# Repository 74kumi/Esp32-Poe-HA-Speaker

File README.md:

# ESP32 PoE Home Assistant Speaker

A PoE-powered network ceiling-speaker controller built around an **ESP32-S3**, **W5500 Ethernet**, **PCM5122 DAC**, and **TPA3116D2 amplifier**.

The long-term goal is a retrofit-friendly Home Assistant / voice-assistant speaker platform: reuse ordinary ceiling speakers, add network audio and control at the speaker, and optionally add a modular microphone-array ring hidden behind the existing grille.

## Project disclaimer

I'm not a hardware engineer — I'm an IT administrator who enjoys electronics, Home Assistant, and building things. I have a working understanding of many of the concepts involved, but this project has also been developed heavily with AI-assisted design, CAD scripting, and review.

I would genuinely welcome review or collaboration from experienced hardware engineers, especially as the project moves toward its first physical prototype.

The finalized engineering handoff is now archived in this repository, but the hardware has not yet been fabricated, assembled, or electrically validated. I cannot claim that the current design will work as intended. Please treat it as an engineering prototype and manufacturing handoff, not a proven product.

> **RevF manufacturing release:** this is the finalized manufacturing handoff for the RevE PCB design. The electrical CAD revision remains RevE for traceability; RevF identifies the released manufacturing package.
>
> The supplied package was reviewed and verified by an engineer according to the project owner. That review evidence is preserved with the handoff, but it does not replace independent source-file review, fabrication, assembly, or prototype validation. PCBWay should confirm the final 4-layer stack-up and 100 Ω Ethernet impedance before production.

## Project status

| Area | Status |
| --- | --- |
| Main-board schematic / PCB | Rev E finalized engineered source archived |
| Main-board manufacturing release | RevF handoff archived with Gerbers, drills, BOM, CPL, STEP, and notes |
| KiCad source | Rev E source available directly in this repository |
| Main-board saved ERC / DRC | Supplied release reports included; profile-dependent and not a substitute for independent validation |
| Ethernet layout | Finalized: 0.2764 mm / 0.20 mm target geometry; fabricator stack-up confirmation remains |
| Power / protection | Finalized engineering handoff; bench startup, fault, current, and thermal validation remain |
| Audio / amplifier | Circuit, thermal, and acoustic validation still required |
| Firmware | ESP32 Voice Home Assistant firmware target; bring-up not yet complete |
| Home Assistant integration | ESP32 Voice Home Assistant integration planned after hardware bring-up |
| Microphone array | Six-microphone RGB ring engineered handoff archived; prototype and acoustic validation remain |
| Physical prototype | Not built yet; fabrication package prepared |

A clean ERC/DRC result is a regression check, not proof that the circuit is electrically correct, safe, acoustically suitable, or production-ready.

## Current hardware

The main board is intended to provide:

- ESP32-S3 controller
- wired Ethernet using W5500
- PoE-powered operation with bench-power support for development
- PCM5122 playback DAC
- TPA3116D2 speaker amplifier
- target of approximately **30 W into 4 ohms**, subject to real prototype validation
- programming / debug access
- expansion interfaces, including the reserved J4 microphone-ring connector

### Current Rev E board preview

The image above reflects the current Rev E board source more closely than the historical 3D render at the top of this README. The KiCad files remain the authoritative design reference.

### Open the Rev E design

The active source is tracked directly in Git:

- [Rev E KiCad project](hardware/PoE-Speaker/RevE/KiCad-RevE/PoE-Speaker-RevE.kicad_pro)
- [Rev E PCB](hardware/PoE-Speaker/RevE/KiCad-RevE/PoE-Speaker-RevE.kicad_pcb)
- [Rev E schematic](hardware/PoE-Speaker/RevE/KiCad-RevE/PoE-Speaker-RevE.kicad_sch)
- [Rev E engineering notes](hardware/PoE-Speaker/RevE/engineering/)
- [RevF manufacturing package](hardware/PoE-Speaker/RevF/Manufacturing/README-PCBWay.md)
- [RevF board preview](board-revf.png)
- [Historical design checkpoints](hardware/checkpoints/)

Open the project in **KiCad 10**. Keep the adjacent project-local footprint library, symbol library, tables, design rules, BOM, and generated netlist together.

## Modular microphone rings

The project now includes a supplied, engineer-reviewed six-microphone RGB ring handoff. It is separate from the main PoE board and is intended to connect through the main-board J4 expansion interface. The ring package includes KiCad source, custom libraries, BOM, placement data, Gerbers, drills, STEP models, datasheets, design notes, and engineering reports.

- [Microphone-ring concept and status](hardware/microphone-rings/README.md)
- [Final six-microphone RGB ring handoff](hardware/microphone-rings/ESP32-S3-Microphone-RGB-Ring/)
- [Listening / status-light plan](hardware/microphone-rings/LED-STATUS-LIGHT-PLAN.md)
- [Main-board J4 connector definition](hardware/PoE-Speaker/RevE/engineering/CONNECTOR-GUIDE.md)

The archived ring is a six-microphone engineered design; it should not be described as an already validated eight-microphone production system. Electrical bring-up, cable/interface validation, mechanical fit, microphone performance, vibration behavior, and acoustic/echo testing remain outstanding.

## Engineering status and roadmap

The current release state is **final engineered PCB handoffs archived**:

- Main board: RevE editable CAD with a RevF manufacturing release package.
- Microphone ring: six-microphone RGB engineered handoff with manufacturing outputs.
- Provenance: supplied final files, reports, and supporting evidence are preserved; embedded history repositories, lock files, and editor session artifacts were excluded.

Remaining work before production approval includes:

1. Confirm the PCBWay 4-layer stack-up, finished thickness, copper assumptions, and 100 Ω Ethernet impedance.
2. Fabricate and assemble a prototype from the RevF handoff.
3. Execute controlled PoE, bench-power, startup, protection, Ethernet, regulator, DAC, amplifier, thermal, and fault testing.
4. Bring up the six-microphone ring through J4 and validate its power, clock/data, I2C/RGB control, cable behavior, and connector pinout.
5. Measure microphone response, vibration coupling, grille fit, acoustic shadowing, simultaneous playback behavior, and echo-cancellation requirements.
6. Complete the ESP32 Voice Home Assistant firmware bring-up and Home Assistant integration after the hardware interfaces are validated.

Project documents:

- [Roadmap](ROADMAP.md)
- [Engineering review guide](ENGINEERING-REVIEW.md)
- [Order / release review](ORDER-RELEASE-REVIEW.md)
- [Prototype validation plan](PROTOTYPE-VALIDATION.md)
- [Contribution guidance](CONTRIBUTING.md)
- [GitHub issues](https://github.com/74kumi/Esp32-Poe-HA-Speaker/issues)

## Repository layout

```text
.
├── docs/
│   ├── HISTORY.md
│   └── images/
│       └── early-board-render.png
├── hardware/
│   ├── PoE-Speaker/
│   │   ├── RevE/
│   │   │   ├── KiCad-RevE/        # current editable board source
│   │   │   └── engineering/       # design reviews, calculations and scripts
│   │   └── RevF/Manufacturing/    # fabrication and assembly release outputs
│   ├── microphone-rings/
│   │   ├── ESP32-S3-Microphone-RGB-Ring/ # engineered ring handoff
│   │   └── README.md              # concept, interface, and validation status
│   └── checkpoints/               # historical board revisions
├── ENGINEERING-REVIEW.md
├── ORDER-RELEASE-REVIEW.md
├── PROTOTYPE-VALIDATION.md
├── ROADMAP.md
└── board-top.png
```

## Contributing / reviewing

Engineering review is welcome, especially around Ethernet signal integrity, protection / fault behavior, power conversion, amplifier implementation, thermal design, footprints, acoustic performance, and manufacturability.

When reporting a hardware finding, please include the affected revision, component / pin / net, location where practical, expected behavior, observed concern, and supporting datasheet section or calculation. Clearly distinguish confirmed defects from questions or suggested improvements.

See [CONTRIBUTING.md](CONTRIBUTING.md) for the current review priorities and main-board change policy.

This project has used AI-assisted CAD scripting and review workflows. AI output is not treated as engineering validation; independent review and physical prototype measurements are still required.

## License

Original hardware design materials are available for personal, educational, research, and other noncommercial use under the terms in [LICENSE](LICENSE).

Commercial manufacture, sale, OEM use, paid integration, or other commercial exploitation requires a separate written commercial license from the copyright holder.

Software, firmware, scripts, and third-party material may be subject to separate terms. Vendor references, library content, trademarks, and datasheets retain their respective owners' rights and notices.

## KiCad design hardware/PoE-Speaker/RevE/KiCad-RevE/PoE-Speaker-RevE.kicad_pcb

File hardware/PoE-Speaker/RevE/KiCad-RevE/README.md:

# Revision E — prototype review checkpoint

Open PoE-Speaker-RevE.kicad_pro in KiCad 10. This is the latest editable board. Earlier revisions remain preserved. NOT APPROVED FOR ORDERING OR POWER-UP.

Saved changes: C11 GVDD bypass is now local on B.Cu at (204.9,111.5), preserving the R15 PLIMIT branch; underside assembly clearance remains part of mechanical review. U7 FSW now connects to 3V3 per TI guidance; all previously missing passive/header order codes have documented candidates; C120/C121 use stable 100nF 100V C0G 1210 parts and C122 uses a 1uF 100V 1210 part. C17/C18 are a matched 2.2uF 25V pair. U5 is TPA3116D2DADR, U9/U10 are LM5050MK-2/NOPB, and Ag5800 is confirmed as the complete U1 code. Corrected 34 footprint assembly attributes and widened 51 power segments to 0.8mm where existing clearance permits.

Validation: zero DRC findings, zero unconnected items, zero ERC findings under the saved rule profile. All 616 connected model pins match schematic and PCB. U6/U7 electrical pin types are reviewed; the root sheet declares power sources after passive elements. These annotations do not prove circuit performance, and other imported pin types remain incomplete. See reports/power-source-review.json. Missing courtyard and some metadata checks remain disabled in the inherited profile; clean DRC does not substitute for physical review.

## Automated ERC/DRC checks

From the repository root, run:

```sh
KICAD_CLI=kicad-cli ./scripts/run-kicad-checks.sh artifacts/kicad
```

The wrapper writes `erc.rpt` and `drc.rpt`. GitHub Actions runs the same command for pull requests and pushes to `main`, retaining reports for 14 days. CI uses KiCad 10.0.5 from the immutable image `kicad/kicad:10.0.5@sha256:182c8005cb775a2c448a4c18681d489f1ff472a761885eba3e08b07e3c0564de`; use KiCad 10.0.5 for local runs when exact CI parity is required. The checks require zero KiCad ERC/DRC violations and do not run DRC after an ERC failure. Project-specific engineering/checkpoint scripts are intentionally excluded from CI because many are board-mutating, depend on checkpoint-local tools/data, or have not yet been proven read-only and reproducible in a clean CI environment.

Clean checks do not prove electrical correctness, PoE isolation, Ethernet signal integrity, thermal safety, manufacturability, or fabrication readiness.

Remaining work before a prototype order:

1. Reroute the remaining narrow loaded power paths, review via current capacity and local switching loops. reports/power-routing-audit.json contains exact positions and UUIDs; separate low-current sense branches from load trunks before modifying them. The two longest 24V_AMP sections (49.385mm and 39.837mm) have now been rerouted at 1.0mm width. A new continuous 1.0mm feed from C5 to the amplifier supply bypasses the congested narrow branch using two 0.5mm drilled vias. The original branch remains in parallel. See engineering/REVE-TRUNK-ROUTING.md; the whole path is not yet current-qualified.
2. Qualify Ethernet differential routing against the explicit JLC04161H-7628 design baseline and verify continuous return paths. See engineering/ETHERNET-STACKUP.md; the calculator-derived Ethernet100 routing preset is saved, but copper still needs rerouting and fabrication confirmation.
3. Review input fuse/transient coordination, capacitor effective capacitance and regulator stability, and amplifier supply tolerance. F1 DC interrupt ratings are now sourced; source/fault and time-current coordination remain open (engineering/FUSE-RATING-REVIEW.md).
4. Fit a top heatsink to the TPA3116D2 DAD package, check the Ag5800 thermal interface, body clearances, mounting support and connector access. H3/H4 now support the extended right edge at x=275; use insulating M2 standoffs. Thirteen assembly components still need verified courtyard/body review.
5. Produce and inspect Gerber, drill, assembly BOM and placement files only after those design checks; obtain fabricator stackup/via-treatment constraints. No manufacturing files or order submission are included in this checkpoint.

After assembly: staged current-limited bring-up, rail/startup/overload measurements, firmware and audio/Ethernet tests. Those are prototype validation activities, not prerequisites that can be completed without hardware. The eight-microphone ring remains a future separate board; this board is not a completed eight-microphone capture system.

Preserve routing: do not run build_revision.py or build_efuse_revision.py over this folder. For schematic-only updates run refresh_prototype_schematic.py, then annotate_prototype_power.py, export netlist/ERC and run validate_prototype.py. Editing model metadata alone does not update the schematic.

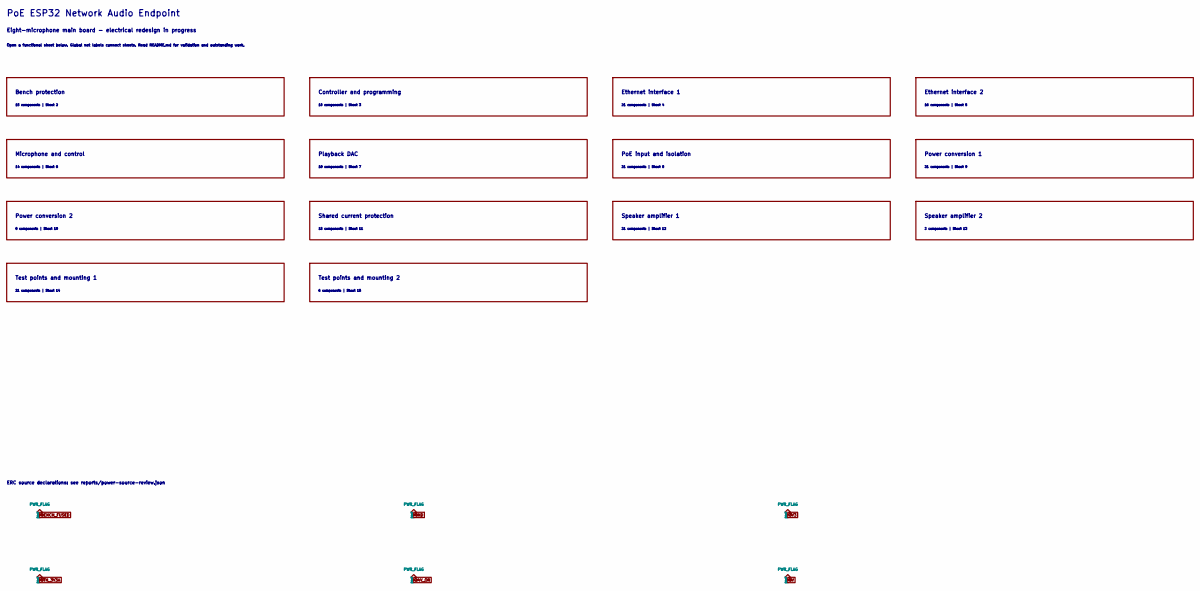
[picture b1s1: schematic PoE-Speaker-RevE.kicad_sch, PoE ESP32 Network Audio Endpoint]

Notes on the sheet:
ERC source declarations: see reports/power-source-review.json
21 components | Sheet 8
Microphone and control
Test points and mounting 1
15 components | Sheet 11
21 components | Sheet 14
21 components | Sheet 12
2 components | Sheet 13
14 components | Sheet 6
Bench protection
18 components | Sheet 7
21 components | Sheet 9
16 components | Sheet 5
Power conversion 1
15 components | Sheet 2
Speaker amplifier 1
Open a functional sheet below. Global net labels connect sheets. Read README.md for validation and outstanding work.
Ethernet interface 2
PoE ESP32 Network Audio Endpoint
Speaker amplifier 2
Shared current protection
Eight-microphone main board - electrical redesign in progress
PoE input and isolation
Playback DAC
Ethernet interface 1
6 components | Sheet 15
Power conversion 2
21 components | Sheet 4
Test points and mounting 2
Controller and programming
8 components | Sheet 10
10 components | Sheet 3

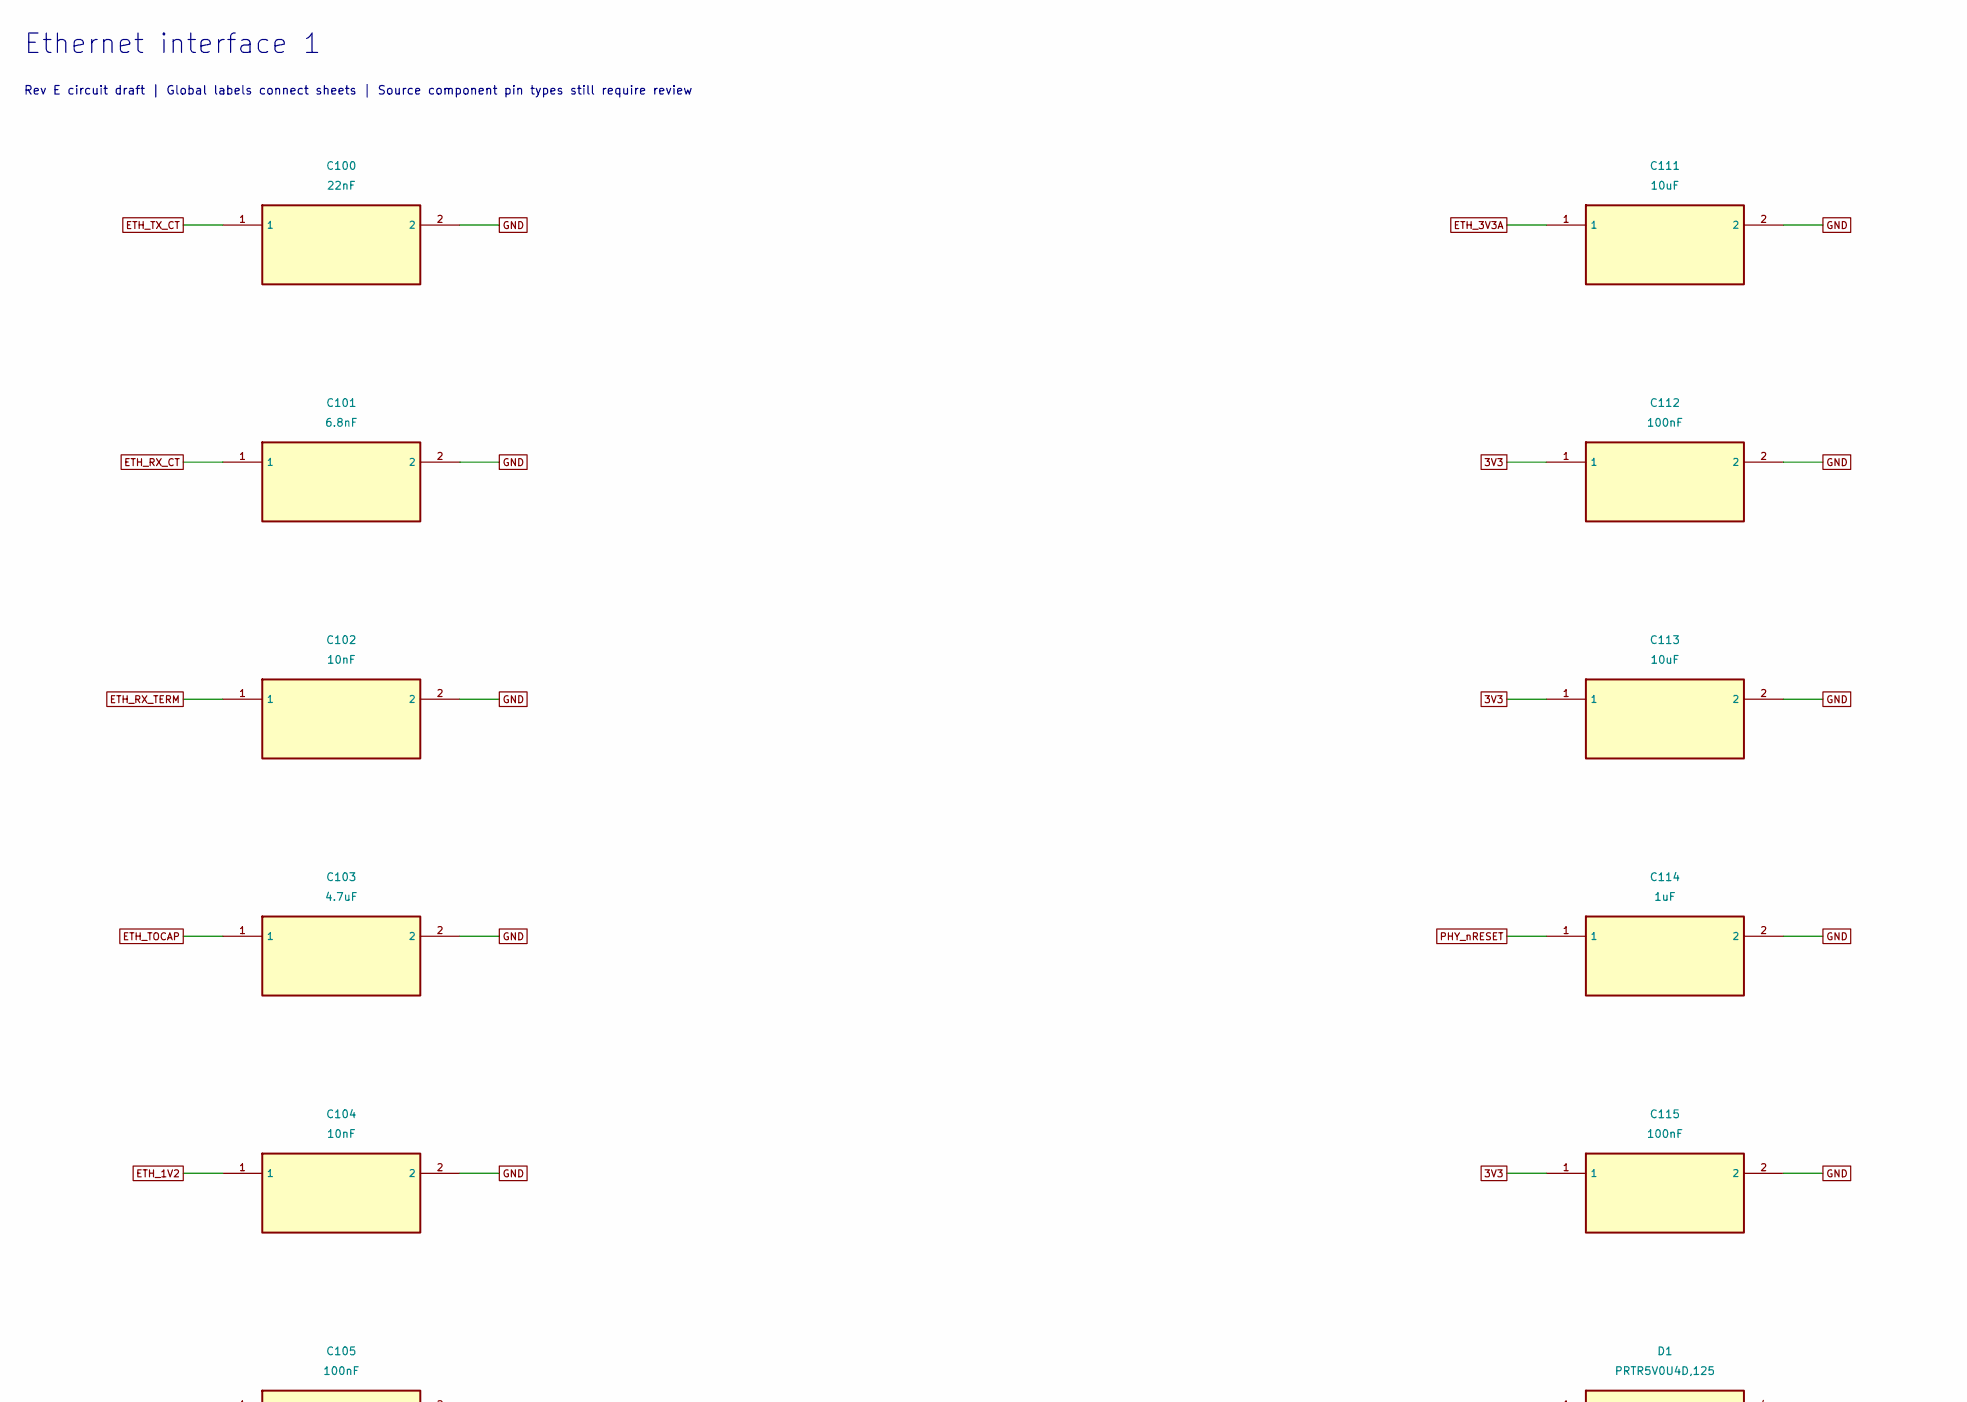
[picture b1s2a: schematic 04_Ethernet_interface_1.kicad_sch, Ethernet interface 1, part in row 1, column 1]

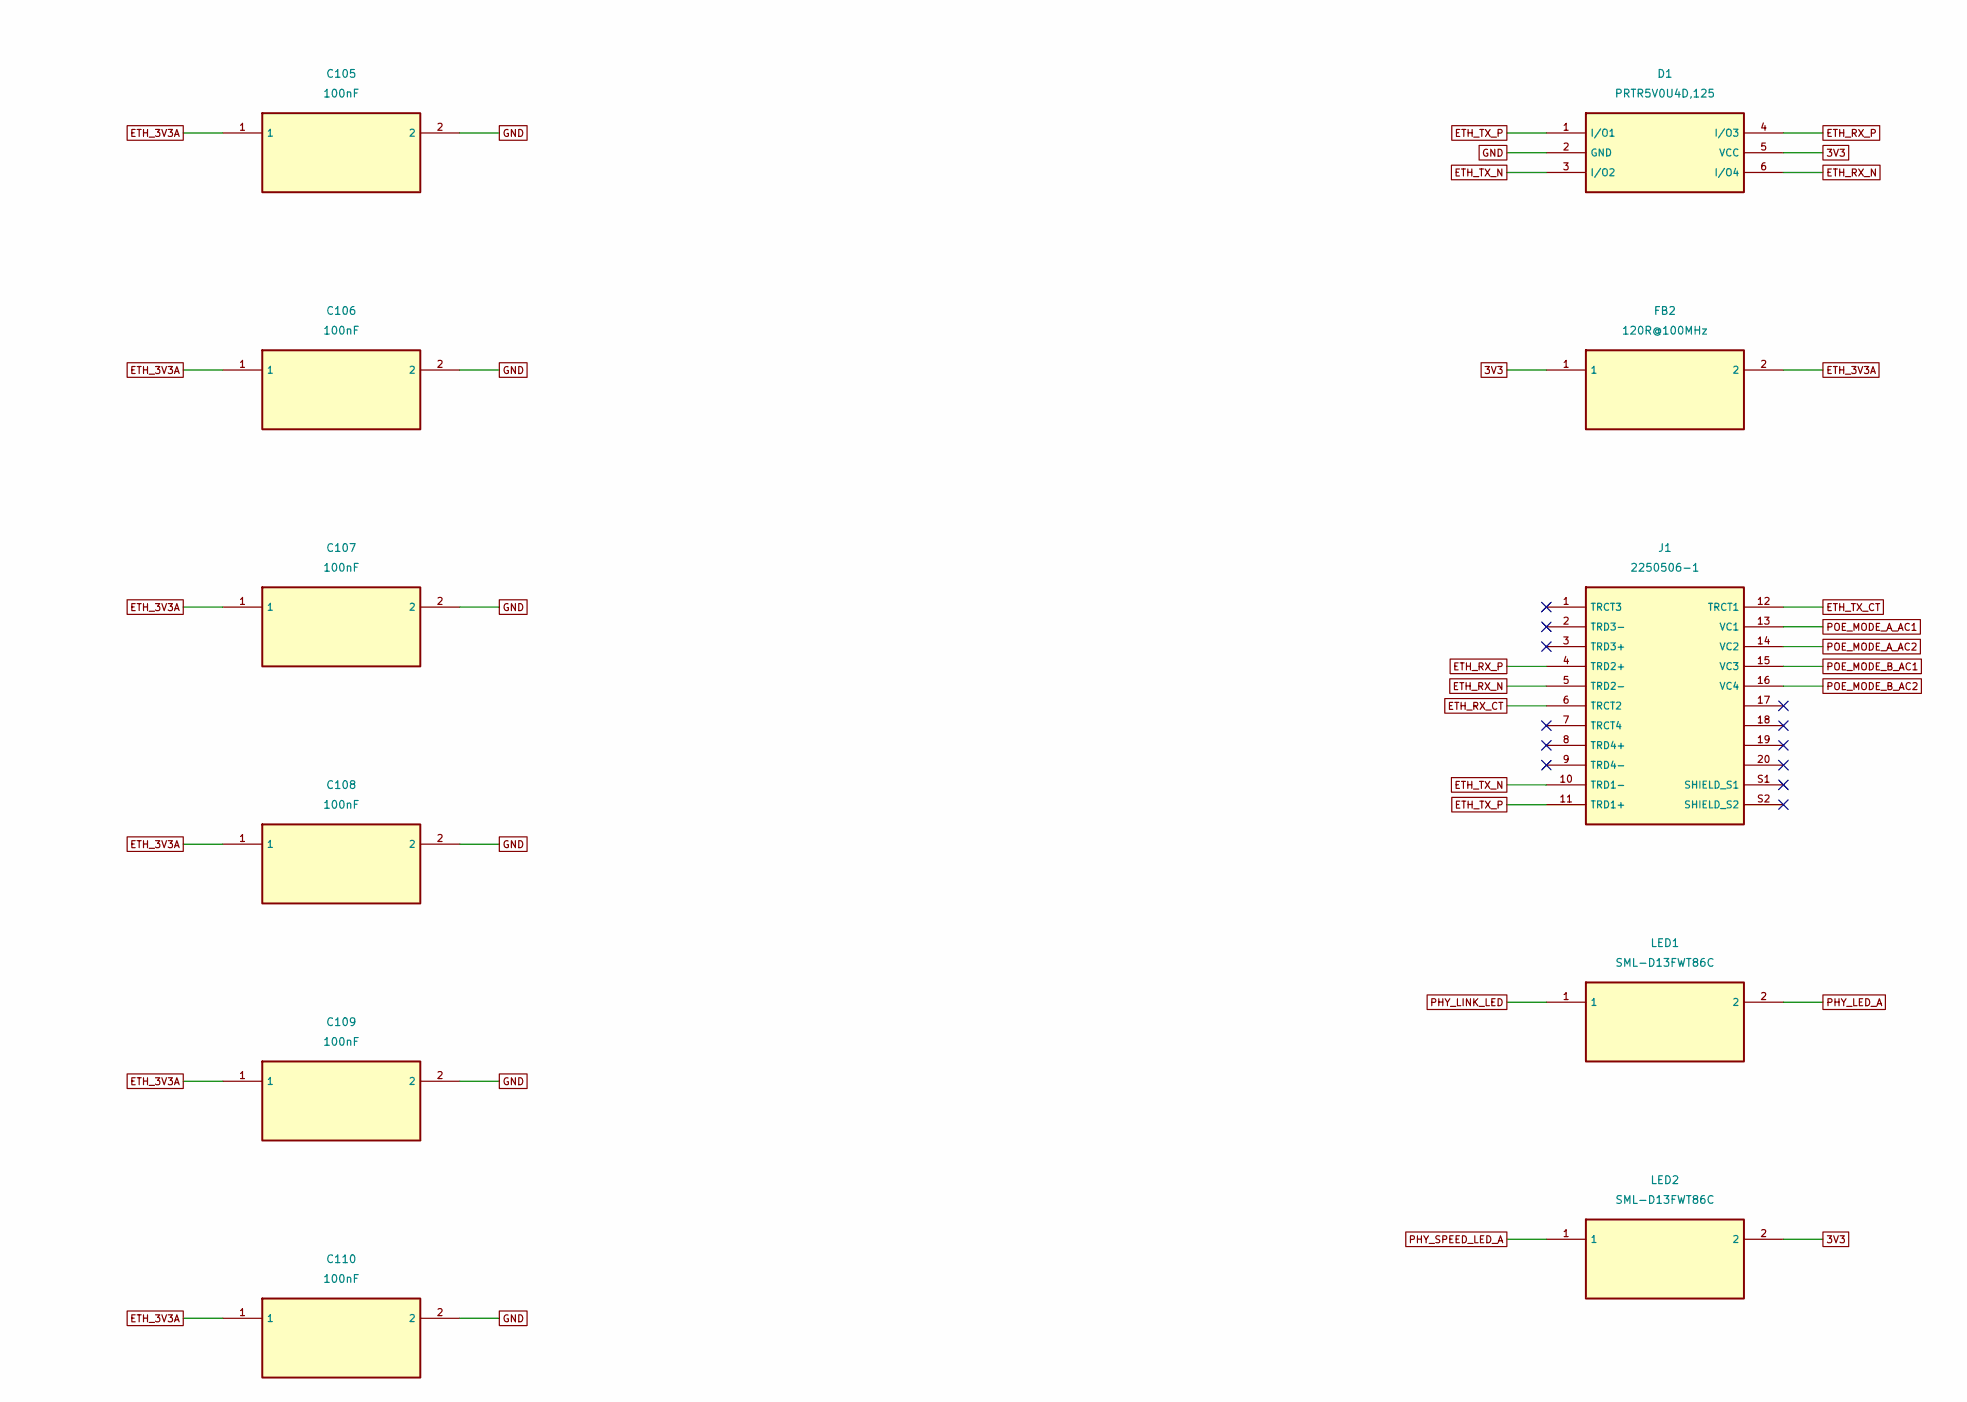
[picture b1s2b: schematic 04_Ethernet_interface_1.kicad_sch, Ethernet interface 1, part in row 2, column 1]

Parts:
C100: 22nF; C100_RevB; Voltage Rating 50 V; Tolerance 10%; Manufacturer Part Number C0603C223K5RACTU
C101: 6.8nF; C101_RevB; Voltage Rating 50 V; Tolerance 5%; Manufacturer Part Number C0603C682J5GACTU
C102: 10nF; C102_RevB; Voltage Rating 50 V; Tolerance 10%; Manufacturer Part Number C0603C103K5RACTU
C103: 4.7uF; C103_RevB; Voltage Rating 16 V; Tolerance 10%; Manufacturer Part Number C0805C475K4RACTU
C104: 10nF; C104_RevB; Voltage Rating 50 V; Tolerance 10%; Manufacturer Part Number C0603C103K5RACTU
C105: 100nF; C105_RevB; Voltage Rating 50 V; Tolerance 10%; Manufacturer Part Number C0603C104K5RACTU
C106: 100nF; C106_RevB; Voltage Rating 50 V; Tolerance 10%; Manufacturer Part Number C0603C104K5RACTU
C107: 100nF; C107_RevB; Voltage Rating 50 V; Tolerance 10%; Manufacturer Part Number C0603C104K5RACTU
C108: 100nF; C108_RevB; Voltage Rating 50 V; Tolerance 10%; Manufacturer Part Number C0603C104K5RACTU
C109: 100nF; C109_RevB; Voltage Rating 50 V; Tolerance 10%; Manufacturer Part Number C0603C104K5RACTU
C110: 100nF; C110_RevB; Voltage Rating 50 V; Tolerance 10%; Manufacturer Part Number C0603C104K5RACTU
C111: 10uF; C111_RevB; Voltage Rating 16 V; Tolerance 10%; Manufacturer Part Number GRM21BR61C106KE15L
C112: 100nF; C112_RevB; Voltage Rating 50 V; Tolerance 10%; Manufacturer Part Number C0603C104K5RACTU
C113: 10uF; C113_RevB; Voltage Rating 16 V; Tolerance 10%; Manufacturer Part Number GRM21BR61C106KE15L
C114: 1uF; C114_RevB; Voltage Rating 16 V; Tolerance 10%; Manufacturer Part Number C0603C105K4RACTU
C115: 100nF; C115_RevB; Voltage Rating 50 V; Tolerance 10%; Manufacturer Part Number C0603C104K5RACTU
D1: PRTR5V0U4D,125; D1_RevB; Manufacturer Part Number PRTR5V0U4D,125
FB2: 120R@100MHz; FB2_RevB; Manufacturer Part Number BLM18PG121SN1D
J1: 2250506-1; J1_RevB; Manufacturer Part Number 2250506-1
LED1: SML-D13FWT86C; LED1_RevB; Manufacturer Part Number SML-D13FWT86C
LED2: SML-D13FWT86C; LED2_RevB; Manufacturer Part Number SML-D13FWT86C

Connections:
3V3: C112.1, C113.1, C115.1, D1.5 (VCC), FB2.1, LED2.2; also elsewhere on the board
ETH_1V2: C104.1; also elsewhere on the board
ETH_3V3A: C105.1, C106.1, C107.1, C108.1, C109.1, C110.1, C111.1, FB2.2; also elsewhere on the board
ETH_RX_CT: C101.1, J1.6 (TRCT2)
ETH_RX_N: D1.6 (I/O4), J1.5 (TRD2-); also elsewhere on the board
ETH_RX_P: D1.4 (I/O3), J1.4 (TRD2+); also elsewhere on the board
ETH_RX_TERM: C102.1; also elsewhere on the board
ETH_TOCAP: C103.1; also elsewhere on the board
ETH_TX_CT: C100.1, J1.12 (TRCT1); also elsewhere on the board
ETH_TX_N: D1.3 (I/O2), J1.10 (TRD1-); also elsewhere on the board
ETH_TX_P: D1.1 (I/O1), J1.11 (TRD1+); also elsewhere on the board
GND: C100.2, C101.2, C102.2, C103.2, C104.2, C105.2, C106.2, C107.2, C108.2, C109.2, C110.2, C111.2, C112.2, C113.2, C114.2, C115.2, D1.2 (GND); also elsewhere on the board
PHY_LED_A: LED1.2; also elsewhere on the board
PHY_LINK_LED: LED1.1; also elsewhere on the board
PHY_SPEED_LED_A: LED2.1; also elsewhere on the board
PHY_nRESET: C114.1; also elsewhere on the board
POE_MODE_A_AC1: J1.13 (VC1); also elsewhere on the board
POE_MODE_A_AC2: J1.14 (VC2); also elsewhere on the board
POE_MODE_B_AC1: J1.15 (VC3); also elsewhere on the board
POE_MODE_B_AC2: J1.16 (VC4); also elsewhere on the board

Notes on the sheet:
Ethernet interface 1
Rev E circuit draft | Global labels connect sheets | Source component pin types still require review

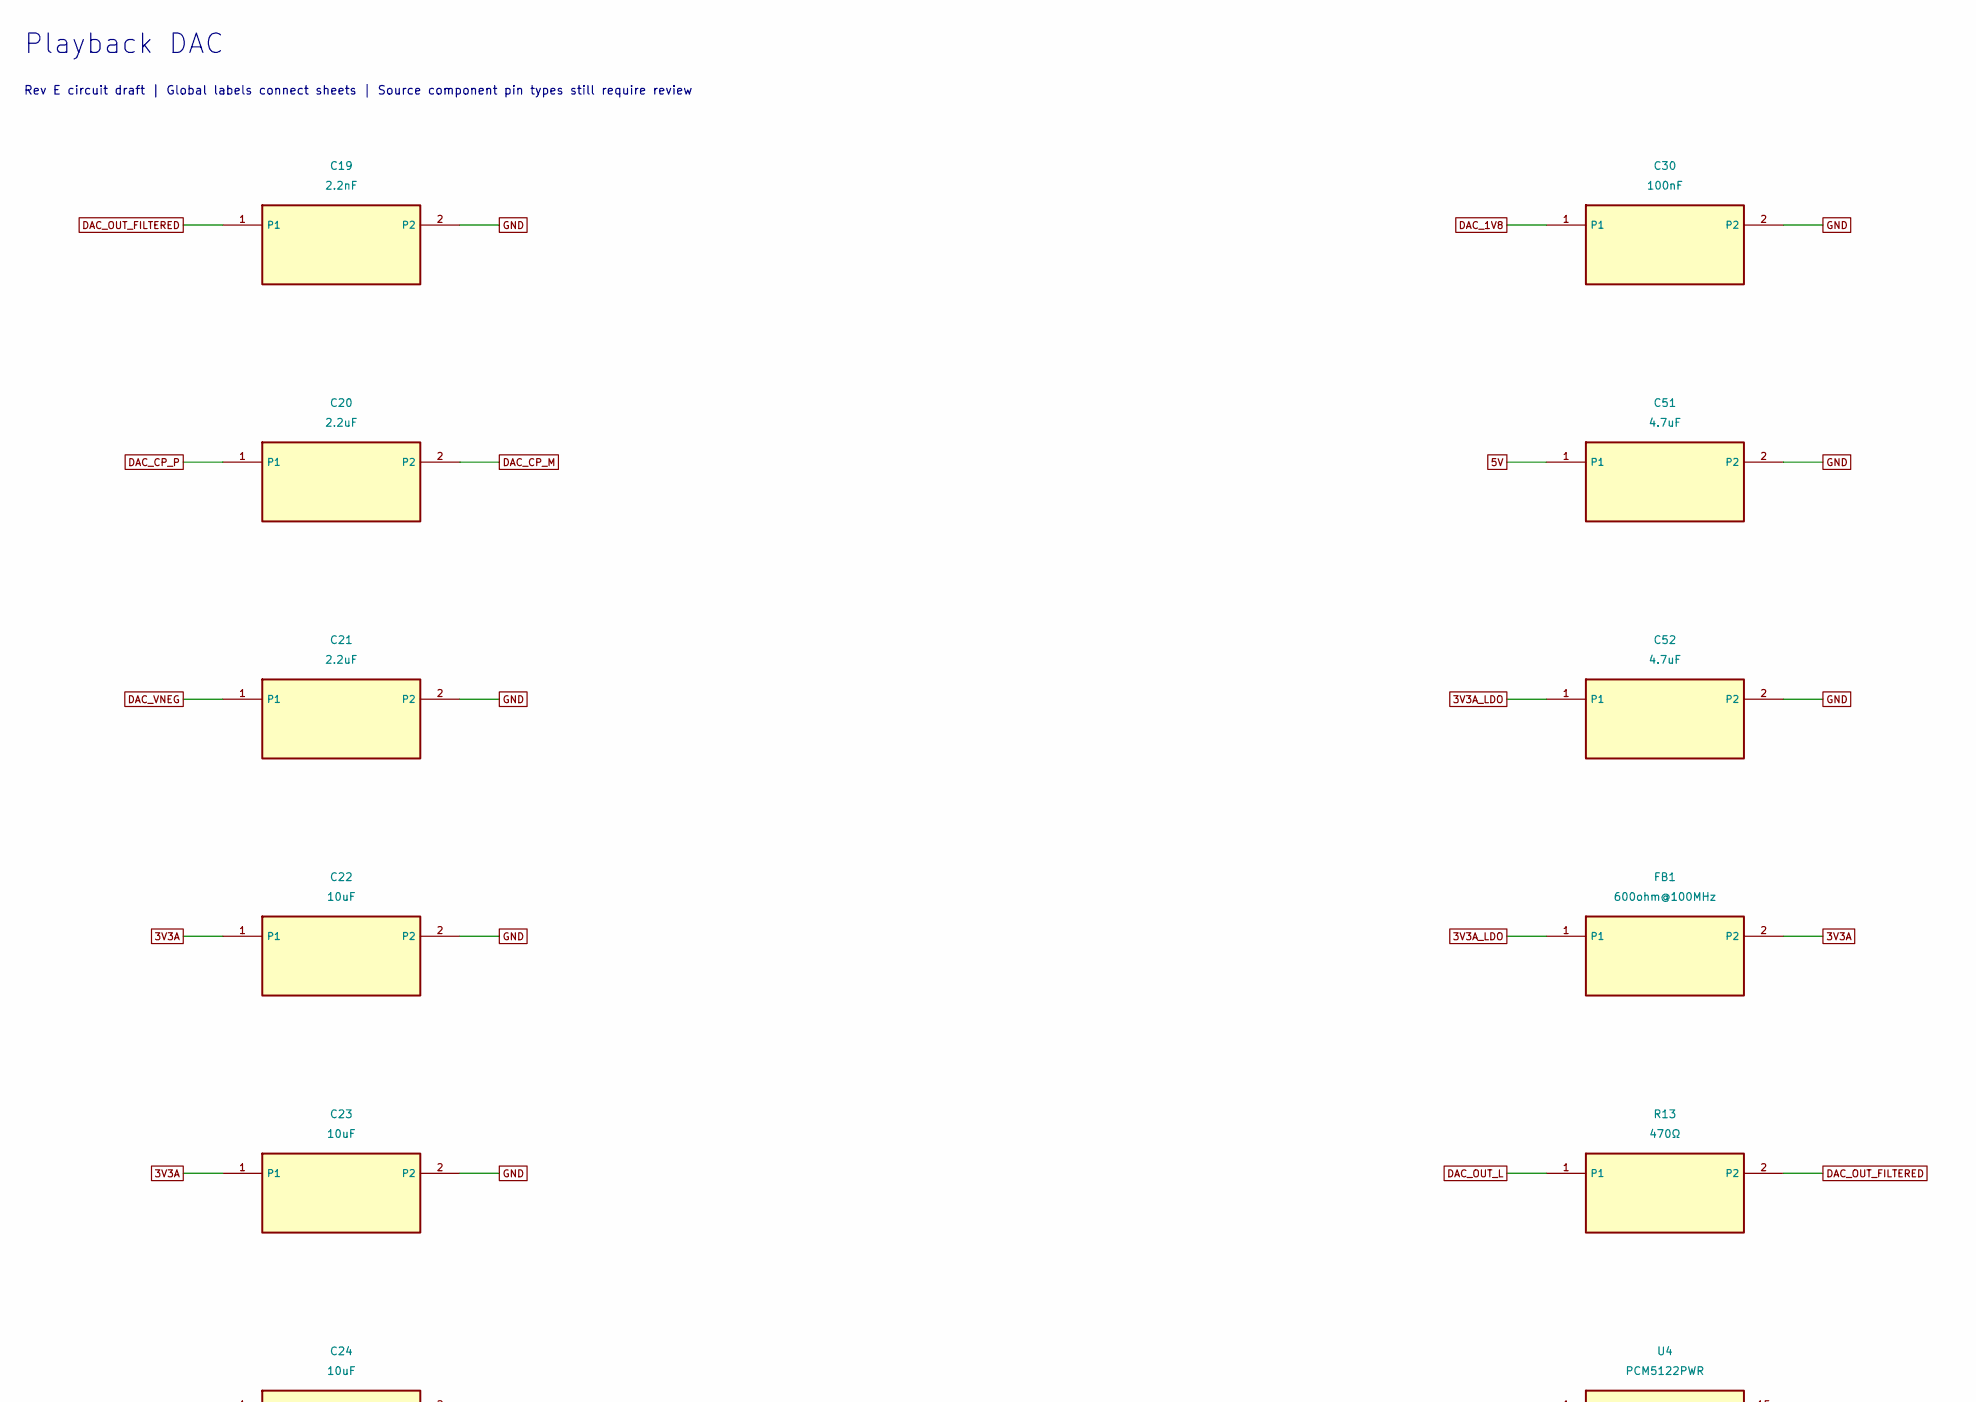
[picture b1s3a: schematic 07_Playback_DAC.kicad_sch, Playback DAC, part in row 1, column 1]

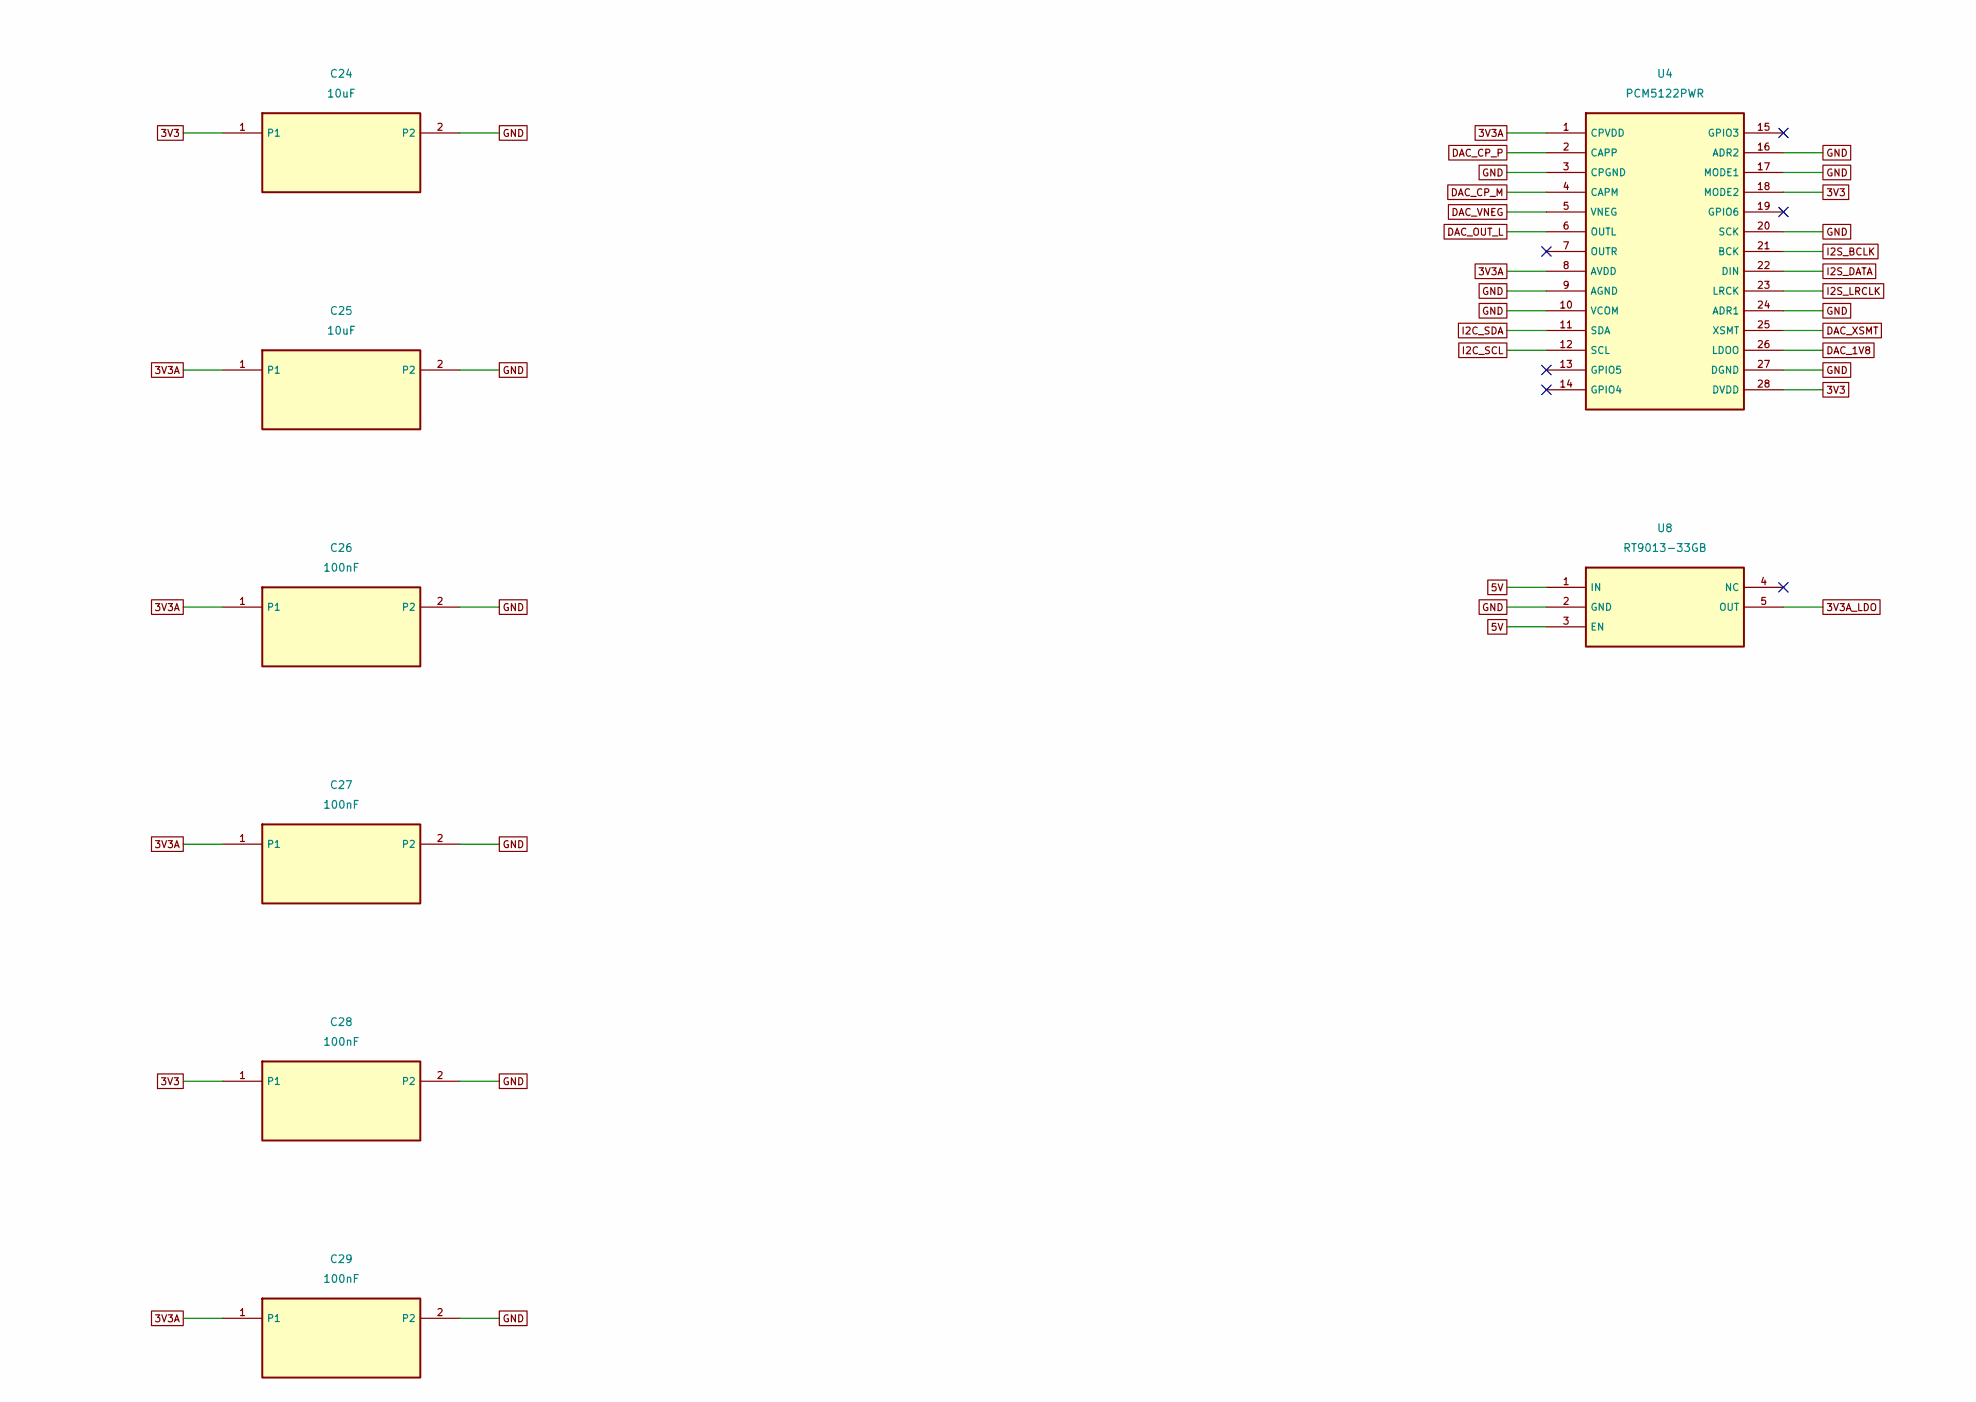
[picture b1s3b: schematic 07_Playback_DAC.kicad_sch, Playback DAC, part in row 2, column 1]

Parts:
C19: 2.2nF; C19_RevB; Voltage Rating 50 V; Tolerance 5%; Manufacturer Part Number C0603C222J5GACTU
C20: 2.2uF; C20_RevB; Voltage Rating 25 V; Tolerance 10%; Manufacturer Part Number C0805C225K3RACTU
C21: 2.2uF; C21_RevB; Voltage Rating 25 V; Tolerance 10%; Manufacturer Part Number C0805C225K3RACTU
C22: 10uF; C22_RevB; Voltage Rating 16 V; Tolerance 10%; Manufacturer Part Number GRM21BR61C106KE15L
C23: 10uF; C23_RevB; Voltage Rating 16 V; Tolerance 10%; Manufacturer Part Number GRM21BR61C106KE15L
C24: 10uF; C24_RevB; Voltage Rating 16 V; Tolerance 10%; Manufacturer Part Number GRM21BR61C106KE15L
C25: 10uF; C25_RevB; Voltage Rating 16 V; Tolerance 10%; Manufacturer Part Number GRM21BR61C106KE15L
C26: 100nF; C26_RevB; Voltage Rating 50 V; Tolerance 10%; Manufacturer Part Number C0603C104K5RACTU
C27: 100nF; C27_RevB; Voltage Rating 50 V; Tolerance 10%; Manufacturer Part Number C0603C104K5RACTU
C28: 100nF; C28_RevB; Voltage Rating 50 V; Tolerance 10%; Manufacturer Part Number C0603C104K5RACTU
C29: 100nF; C29_RevB; Voltage Rating 50 V; Tolerance 10%; Manufacturer Part Number C0603C104K5RACTU
C30: 100nF; C30_RevB; Voltage Rating 50 V; Tolerance 10%; Manufacturer Part Number C0603C104K5RACTU
C51: 4.7uF; C51_RevB; Voltage Rating 16 V; Tolerance 10%; Manufacturer Part Number C0805C475K4RACTU
C52: 4.7uF; C52_RevB; Voltage Rating 16 V; Tolerance 10%; Manufacturer Part Number C0805C475K4RACTU
FB1: 600ohm@100MHz; FB1_RevB; Current Rating 0.5A; Current rating 500 mA; Part Type Inductor
R13: 470Ω; R13_RevB; Tolerance 1%; Power rating 0.10 W conservative; Part Type Resistor
U4: PCM5122PWR; U4_RevB; Part Type Digital To Analog Converters (DACs); JLCPCB Part Class Extended Part
U8: RT9013-33GB; U8_RevB; Manufacturer Part Number RT9013-33GB

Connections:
3V3: C24.1, C28.1, U4.18 (MODE2), U4.28 (DVDD); also elsewhere on the board
3V3A: C22.1, C23.1, C25.1, C26.1, C27.1, C29.1, FB1.2, U4.1 (CPVDD), U4.8 (AVDD); also elsewhere on the board
3V3A_LDO: C52.1, FB1.1, U8.5 (OUT)
5V: C51.1, U8.1 (IN), U8.3 (EN); also elsewhere on the board
DAC_1V8: C30.1, U4.26 (LDOO)
DAC_CP_M: C20.2, U4.4 (CAPM)
DAC_CP_P: C20.1, U4.2 (CAPP)
DAC_OUT_FILTERED: C19.1, R13.2; also elsewhere on the board
DAC_OUT_L: R13.1, U4.6 (OUTL)
DAC_VNEG: C21.1, U4.5 (VNEG)
DAC_XSMT: U4.25 (XSMT); also elsewhere on the board
GND: C19.2, C21.2, C22.2, C23.2, C24.2, C25.2, C26.2, C27.2, C28.2, C29.2, C30.2, C51.2, C52.2, U4.3 (CPGND), U4.9 (AGND), U4.10 (VCOM), U4.16 (ADR2), U4.17 (MODE1), U4.20 (SCK), U4.24 (ADR1), U4.27 (DGND), U8.2 (GND); also elsewhere on the board
I2C_SCL: U4.12 (SCL); also elsewhere on the board
I2C_SDA: U4.11 (SDA); also elsewhere on the board
I2S_BCLK: U4.21 (BCK); also elsewhere on the board
I2S_DATA: U4.22 (DIN); also elsewhere on the board
I2S_LRCLK: U4.23 (LRCK); also elsewhere on the board

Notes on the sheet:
Playback DAC
Rev E circuit draft | Global labels connect sheets | Source component pin types still require review

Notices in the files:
parts and their libraries:
License: https://creativecommons.org/licenses/by/4.0
Copyright 2016 Accelerated Designs. All rights reserved.
